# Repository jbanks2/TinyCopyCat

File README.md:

# TinyCopyCat

Brief: 2 channel servo signal active 3-way splitter.

PCB work done in KiCad (http://kicad-pcb.org/download/)
Code work done in AVR studio (http://www.atmel.com/tools/ATMELSTUDIO.aspx)

Contact Jesse 503.781.5893

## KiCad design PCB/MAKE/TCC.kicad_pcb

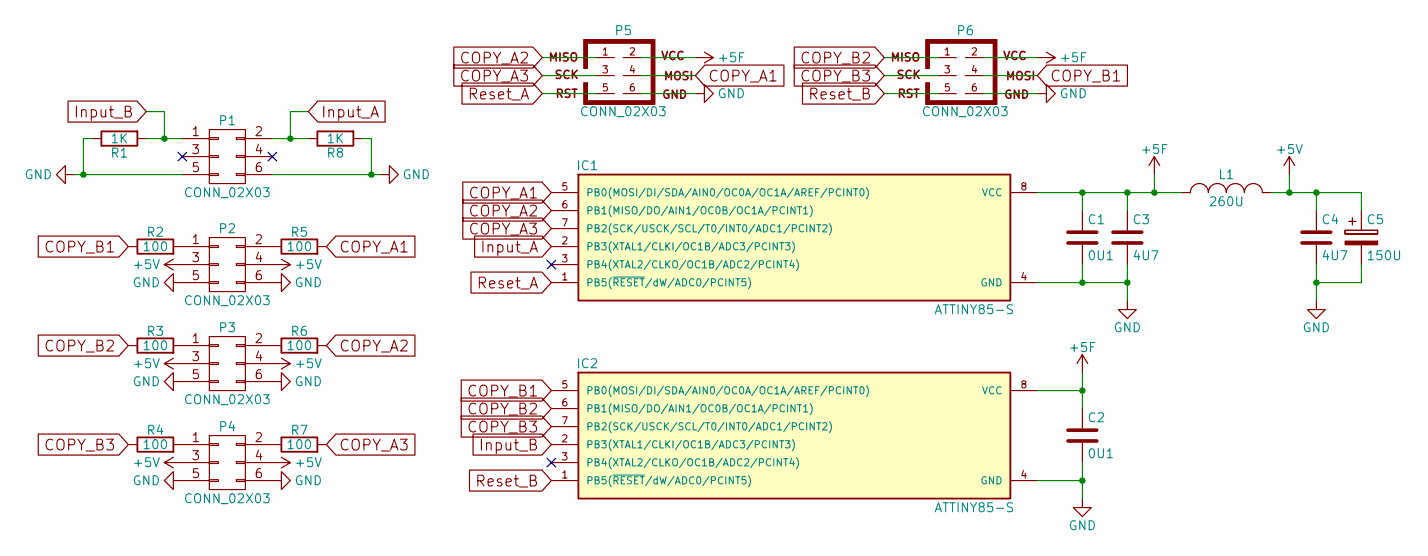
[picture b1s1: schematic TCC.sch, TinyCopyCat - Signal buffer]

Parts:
C1, C2: 0U1; C_0603_HandSoldering; MouserPN 810-C1608X7R1E104K
C3, C4: 4U7; C_1206_HandSoldering; MouserPN 581-12063C475KAT2A
C5: 150U; c_elec_6.3x7.7; MouserPN 710-875105345011
IC1, IC2: ATTINY85-S; SOIC-8_3.9x4.9mm_Pitch1.27mm; MouserPN 556-ATTINY85-20SU
L1: 260U; C_0805_HandSoldering; MouserPN 652-SRF2012A-261YA
P1, P2, P3, P4, P5, P6: CONN_02X03; Pin_Header_Angled_2x03; MouserPN 571-826953-3
R1, R8: 1K; R_0603_HandSoldering; MouserPN 71-CRCW0603-1.0K-E3
R2, R3, R4, R5, R6, R7: 100; R_0603_HandSoldering; MouserPN 71-CRCW0603-100-E3

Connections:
+5F: C1.1, C2.1, C3.1, IC1.8 (VCC), IC2.8 (VCC), L1.1, P5.2, P6.2
+5V: C4.1, C5.1, L1.2, P2.3, P2.4, P3.3, P3.4, P4.3, P4.4
COPY_A1: IC1.5 (PB0(MOSI/DI/SDA/AIN0/OC0A/OC1A/AREF/PCI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), P5.4, R5.2
COPY_A2: IC1.6 (PB1(MISO/DO/AIN1/OC0B/OC1A/PCINT1)), P5.1, R6.2
COPY_A3: IC1.7 (PB2(SCK/USCK/SCL/T0/INT0/ADC1/PCINT2)), P5.3, R7.2
COPY_B1: IC2.5 (PB0(MOSI/DI/SDA/AIN0/OC0A/OC1A/AREF/PCI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), P6.4, R2.1
COPY_B2: IC2.6 (PB1(MISO/DO/AIN1/OC0B/OC1A/PCINT1)), P6.1, R3.1
COPY_B3: IC2.7 (PB2(SCK/USCK/SCL/T0/INT0/ADC1/PCINT2)), P6.3, R4.1
GND: C1.2, C2.2, C3.2, C4.2, C5.2, IC1.4 (GND), IC2.4 (GND), P1.5, P1.6, P2.5, P2.6, P3.5, P3.6, P4.5, P4.6, P5.6, P6.6, R1.1, R8.2
Input_A: IC1.2 (PB3(XTAL1/CLKI/OC1B/ADC3/PCINT3)), P1.2, R8.1
Input_B: IC2.2 (PB3(XTAL1/CLKI/OC1B/ADC3/PCINT3)), P1.1, R1.2
unnamed: P2.1, R2.2
unnamed: P2.2, R5.1
unnamed: P3.1, R3.2
unnamed: P3.2, R6.1
unnamed: P4.1, R4.2
unnamed: P4.2, R7.1
Reset_A: IC1.1 (PB5(~RESET~/dW/ADC0/PCINT5)), P5.5
Reset_B: IC2.1 (PB5(~RESET~/dW/ADC0/PCINT5)), P6.5

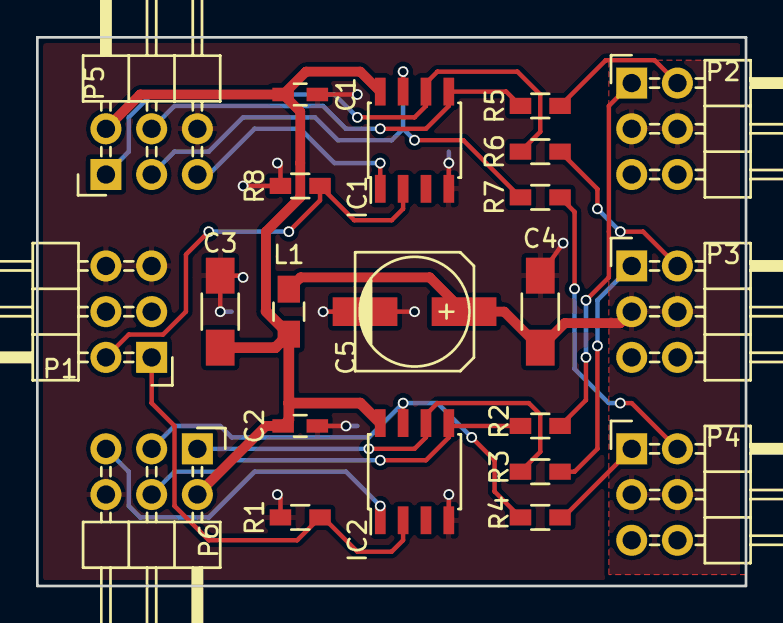
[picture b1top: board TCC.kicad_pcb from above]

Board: 2 copper layers, 39.4 x 30.5 mm, 22 parts (0 on the bottom side), 19 nets.

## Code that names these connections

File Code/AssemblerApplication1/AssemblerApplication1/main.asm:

;
; AssemblerApplication1.asm
;
; Created: 4/26/2016 1:18:55 PM
; Author : jbanks2
;


; Replace with your application code
/*
 * AssemblerApplication1.asm
 *
 *  Created: 12/10/2014 1:55:46 PM
 *   Author: Jesse
 */

.include "tn85def.inc"

.equ    signal = pb3
.equ	power = pb4
.equ    copy1 = pb0
.equ    copy2 = pb1
.equ    copy3 = pb2
.equ	copymask = (1<<copy1)|(1<<copy2)|(1<<copy3)
.org 0
rjmp    reset

.org 20
reset:

start:
 ;port setup 
 ldi	r16,copymask
 out    ddrb,r16
 ldi	r17,(1<<signal)	//set pullup on input
 out	portb,r17
 
loop:
 sbis   pinb,signal       ;skip if pin 1
 rjmp   loop            ;wait till step is set.
 
 out	portb,r16
loop2:
 sbic   pinb,signal       ;skip if step signal to drops
 rjmp   loop2           ;loop until drop
 
 out	portb,r17
 rjmp   start           ;go to start

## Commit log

2016-04-28 First pass at PCB
    layout not finished
2016-04-28 First pass done
2016-04-28 Added the program for the tiny85s
2016-05-26 sdflgi
2016-10-10 bought
